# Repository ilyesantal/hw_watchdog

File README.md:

creator: Antal Ilyes
date: January 2022 - February 2022

This repository was made to contain the development files of a hardware watchdog project for SoftFlex kft.

The hardware watchdog is made of a PCB and a program written in embedded C.

The device is controlled by an ATTyin10 microcontroller. It periodically gets an "alive" tick from the devices connected to it. When an input is driven high, it also turns on a green LED (through an NPN transistor), to visualize it. There is also a red LED indicating the device is powered.

There are two channels that the device can control, as there are only 4 pins on the ATTiny10.

The printed circuit board project can be found under the PCB library. The design was made with KiCAD 6.0

The program works in the following way:

  Initialization: The pins of the microcontroller are set. The corresponding pins to output and to input. The input pins' internal pull-up resistors are also enabled. Then the timer which counts the time passed since the last tick is initialized. Lastly, the interrupts are set up for the input pins.
  
  Timer: There is only one timer in the ATTiny10, so everything has to be done in this. For every trigger (which happens in a frequency that can be set up using the defines), it checks the status of both devices. If the device is inactive, there is nothing to do. If a device is in init status, it is counting the time between the first two ticks. If the device is in active mode, the timer counts the time passed since the last tick.
  
  Input: When an input is driven high, it triggers an interrupt. In the ISR (Interrupt Service Routine) the program determines which input generated the interrupt (as the interrupt vector cannot distinguish which pin did, it triggers when any set pin is triggered), then checks the currenct status of the device corresponding to the pin, and changes the status based on that.
  
  Main loop: If there is a device, which reached the point, where it should be reset, it is indicated to the main loop by the counter which shows that there is a time for which the output should be driven high (which makes the relay to switch off). After it was driven high for the given time, it sets the output back to low.

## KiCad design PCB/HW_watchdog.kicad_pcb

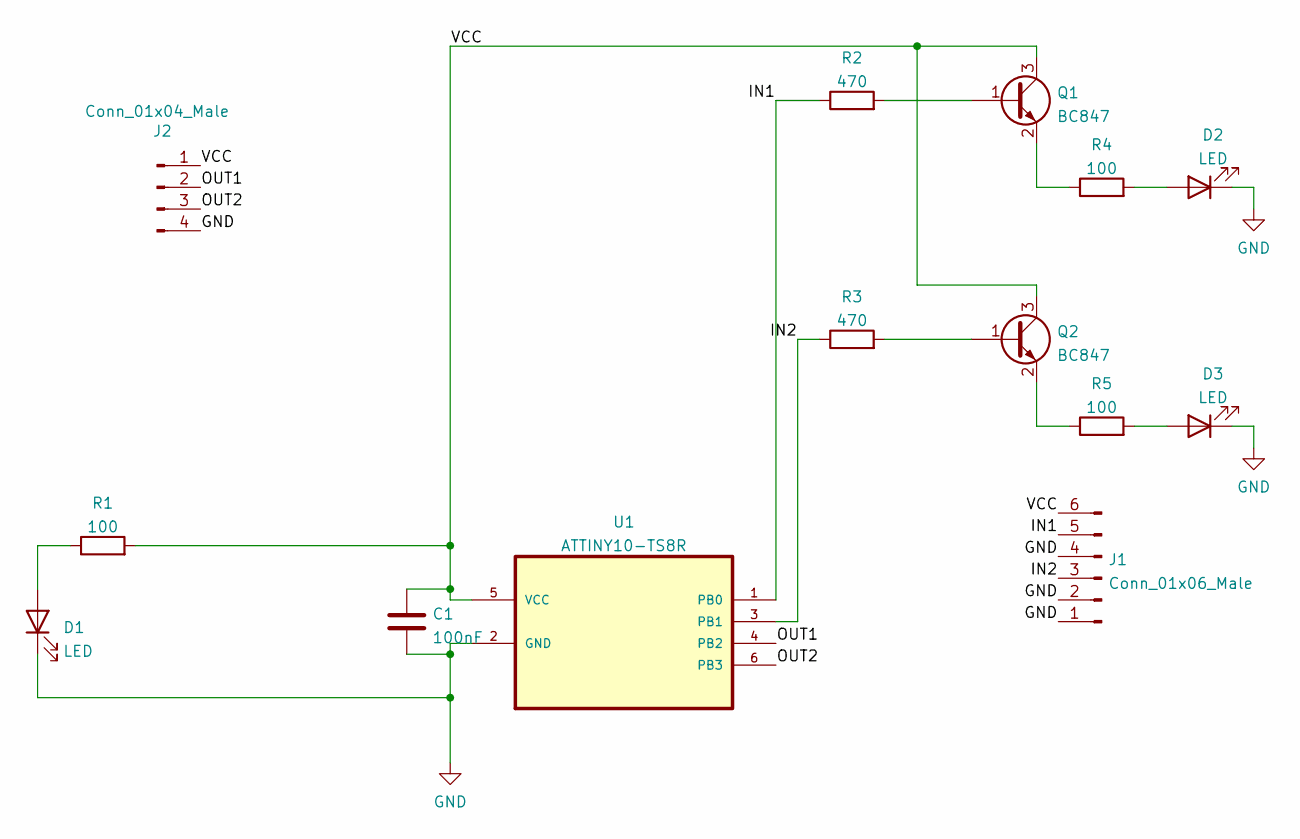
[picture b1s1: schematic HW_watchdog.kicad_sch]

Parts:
C1: 100nF; D_1206_3216Metric
D1, D2, D3: LED; LED_1206_3216Metric
J1: Conn_01x06_Male; PinHeader_1x06_P2.54mm_Horizontal
J2: Conn_01x04_Male; PinSocket_1x04_P2.54mm_Vertical
Q1, Q2: BC847; SOT-23
R1, R4, R5: 100; R_1206_3216Metric
R2, R3: 470; R_1206_3216Metric
U1: ATTINY10-TS8R; ATTiny10-TS8R; MPN ATTINY10-TS8R

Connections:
/IN1: J1.5, R2.1, U1.1 (PB0)
/IN2: J1.3, R3.1, U1.3 (PB1)
/OUT1: J2.2, U1.4 (PB2)
/OUT2: J2.3, U1.6 (PB3)
/VCC: C1.1, J1.6, J2.1, Q1.3 (C), Q2.3 (C), R1.2, U1.5 (VCC)
GND: C1.2, D1.1 (K), D2.1 (K), D3.1 (K), J1.1, J1.2, J1.4, J2.4, U1.2 (GND)
unnamed: D1.2 (A), R1.1
unnamed: D2.2 (A), R4.2
unnamed: D3.2 (A), R5.2
unnamed: Q1.1 (B), R2.2
unnamed: Q1.2 (E), R4.1
unnamed: Q2.1 (B), R3.2
unnamed: Q2.2 (E), R5.1

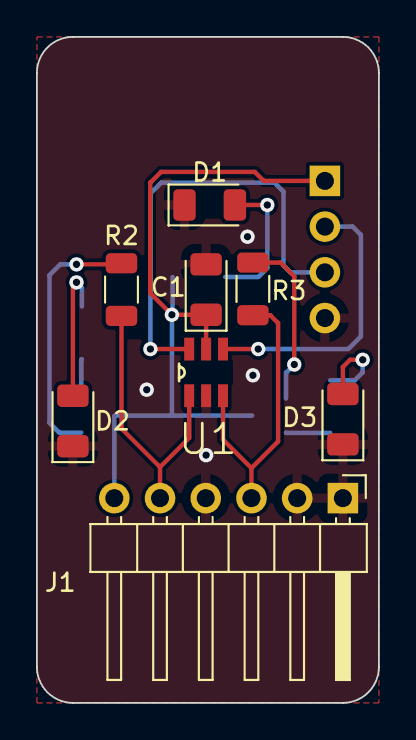
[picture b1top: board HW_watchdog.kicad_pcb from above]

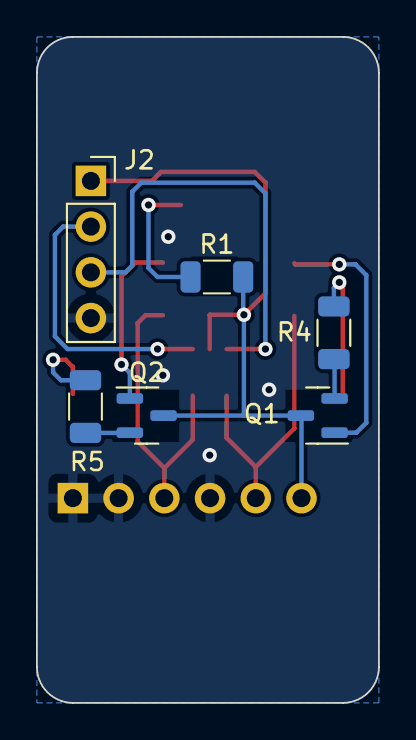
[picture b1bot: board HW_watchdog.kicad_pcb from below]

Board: 2 copper layers, 19.0 x 37.0 mm, 14 parts (6 on the bottom side), 13 nets.

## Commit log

2022-01-10 added files
2022-01-10 pin changed
2022-02-02 moved pcb to new folder, added software
2022-02-02 some modifications
2022-02-05 tested, working
2022-02-17 Project finished
